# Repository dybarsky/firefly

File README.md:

# FireFly

A harware device to attach to Frisbee flying disk to highlight

PCB design:  
<image height="300" src="media/pcb.png"/> <image height="300" src="media/nets.png"/>

PCB render:  
<image height="300" src="media/render-back.png"/> <image height="300" src="media/render-front.png"/>

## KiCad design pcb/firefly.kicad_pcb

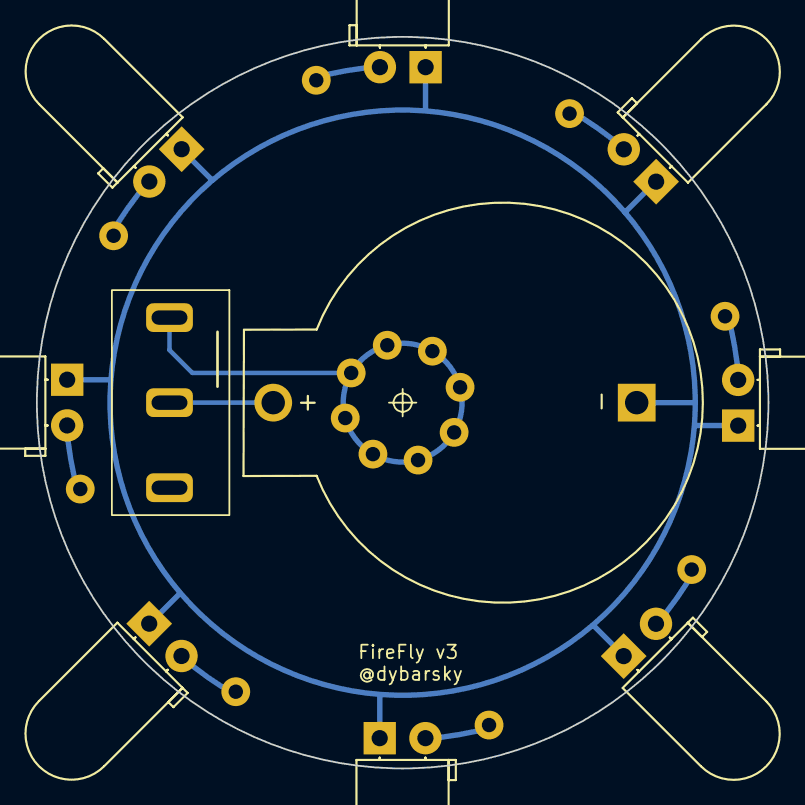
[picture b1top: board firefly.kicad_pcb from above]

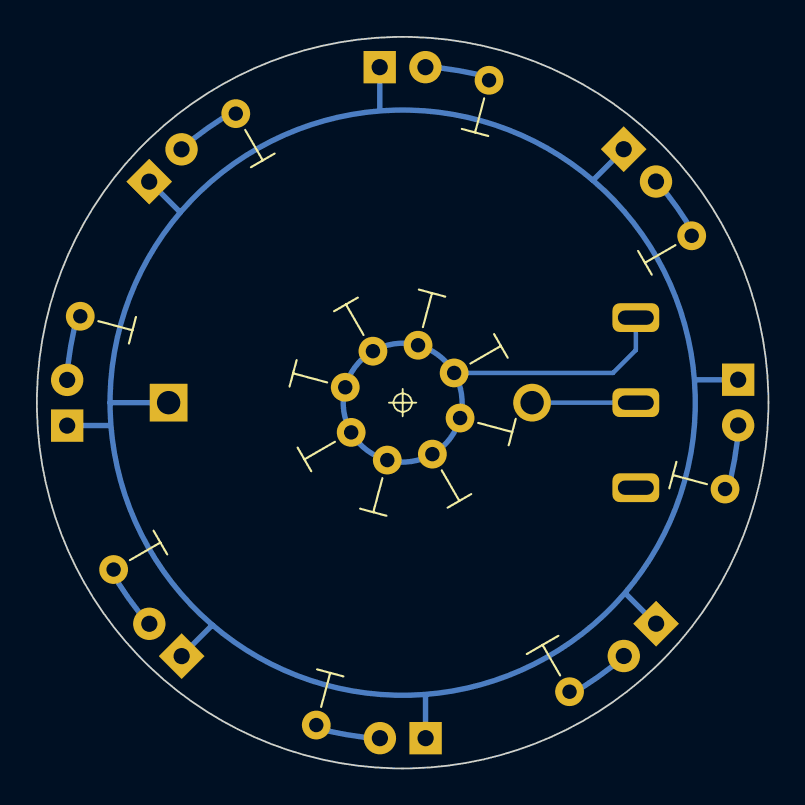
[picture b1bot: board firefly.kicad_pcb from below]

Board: 2 copper layers, 40.6 x 40.6 mm, 12 parts (8 on the bottom side), 3 nets.

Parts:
3: R_Axial_DIN0309_L9.0mm_D3.2mm_P15.24mm_Horizontal
CR2023: BatteryHolder_CR2032
D1, D2, D8: LED_D5.0mm_Horizontal_O1.27mm_Z3.0mm
R1, R2, R4, R5, R6, R7, R8: R_Axial_DIN0309_L9.0mm_D3.2mm_P15.24mm_Horizontal

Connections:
3V: 3.1, CR2023.1, R1.1, R2.1, R4.1, R5.1, R6.1, R7.1, R8.1
GND: CR2023.2, D1.1, D2.1, D8.1
LED: 3.2, D1.2, D2.2, D8.2, R1.2, R2.2, R4.2, R5.2, R6.2, R7.2, R8.2

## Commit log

2025-02-20 Add gitignore file
2025-02-20 Add KiCad project files
2025-02-20 Add Gerber production files
2025-02-20 Add media files
2025-02-20 Add README.md
